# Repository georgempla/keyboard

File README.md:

# George’s Keyboard

After many hours of work, I designed a custom mechanical keyboard featuring RGB LEDs, OLED displays, and rotary encoders. This project focuses on PCB planning, firmware research, CAD design, and represents my second hardware project ever.

---

## What This Project Is

This Project is a custom mechanical keyboard powered by a Raspberry Pi Pico. It has:
- Sections of addressable RGB LEDs
- Two rotary encoders with switches
- An OLED 0.91Inch display
- A custom PCB designed in KiCad
- A 3D-printed case that showcases the PCB

The goal of this project was to recreate my own keyboard layout while adding extra functionality and learning more about PCB design and KMK firmware.

---

## Inspiration

This was only my second project ever. While looking for ideas I realized that the inspiration was right in front of me: my own keyboard. After taking measurements and studying how keyboards in general are designed, I decided to recreate it while adding my own twist on the concept with LEDs, an OLED display, and rotary encoders.

---

## Challenges / What I Learned

This was the second PCB I havee ever designed, and the first one I designed completely on my own. Through this process, I learned:
- How to organize a KiCad project properly
- Better routing techniques
- How to recover from mistakes and reroute a board cleanly

Even though I had to redo parts of the design, the second iteration was much cleaner.

---

## Design Files

This project includes:
- A full keyboard schematic
- A routed PCB layout
- A 3D printable case design

Schematic | PCB Layout | Case
:--:|:--:|:--:
 |  |  

---

## Firmware (Planned)

The firmware is currently written but *untested*, as the keyboard has not yet been assembled. Once the hardware is built I plan to:
- Flash the firmware to the Raspberry Pi Pico
- Test all keys, LEDs, encoders, and the OLED display
- Fix bugs and upload a finalized version

After testing this section will be updated with corrected code and flashing instructions.

---

## Bill of Materials (BOM)

### Electronics
- 1× Raspberry Pi Pico
- 1× OLED module (0.91", 128×32)
- 2× Rotary encoders (12 mm, 24 P/R, with switch)
- 10× SK6812 RGB LEDs
- 2× 74HCT595D shift registers
- 1× 74AHCT125
- 110× 1N4148 diodes
- 1× 1000 µF capacitor
- 2× 100 nF ceramic capacitors

### Mechanical
- Keychron K Pro switches (110 pieces)
- Glorious Stabilizers V2
- Mountain Dolomite A Backlit Keycap Set
- 3D printed case (`case.stl`)

---

## Next Steps

- Wait for approval
- Order the PCB
- Print the case
- Assemble and solder all components
- Test and debug firmware
- Update this README with build instructions

---

## Reflection

This project helped me evolve a lot as a designer. Compared to my first PCB, this one is cleaner, more complex, and better planned. Even though it isn't built yet, I learned a huge amount about schematics, routing, and hardware design through the process.

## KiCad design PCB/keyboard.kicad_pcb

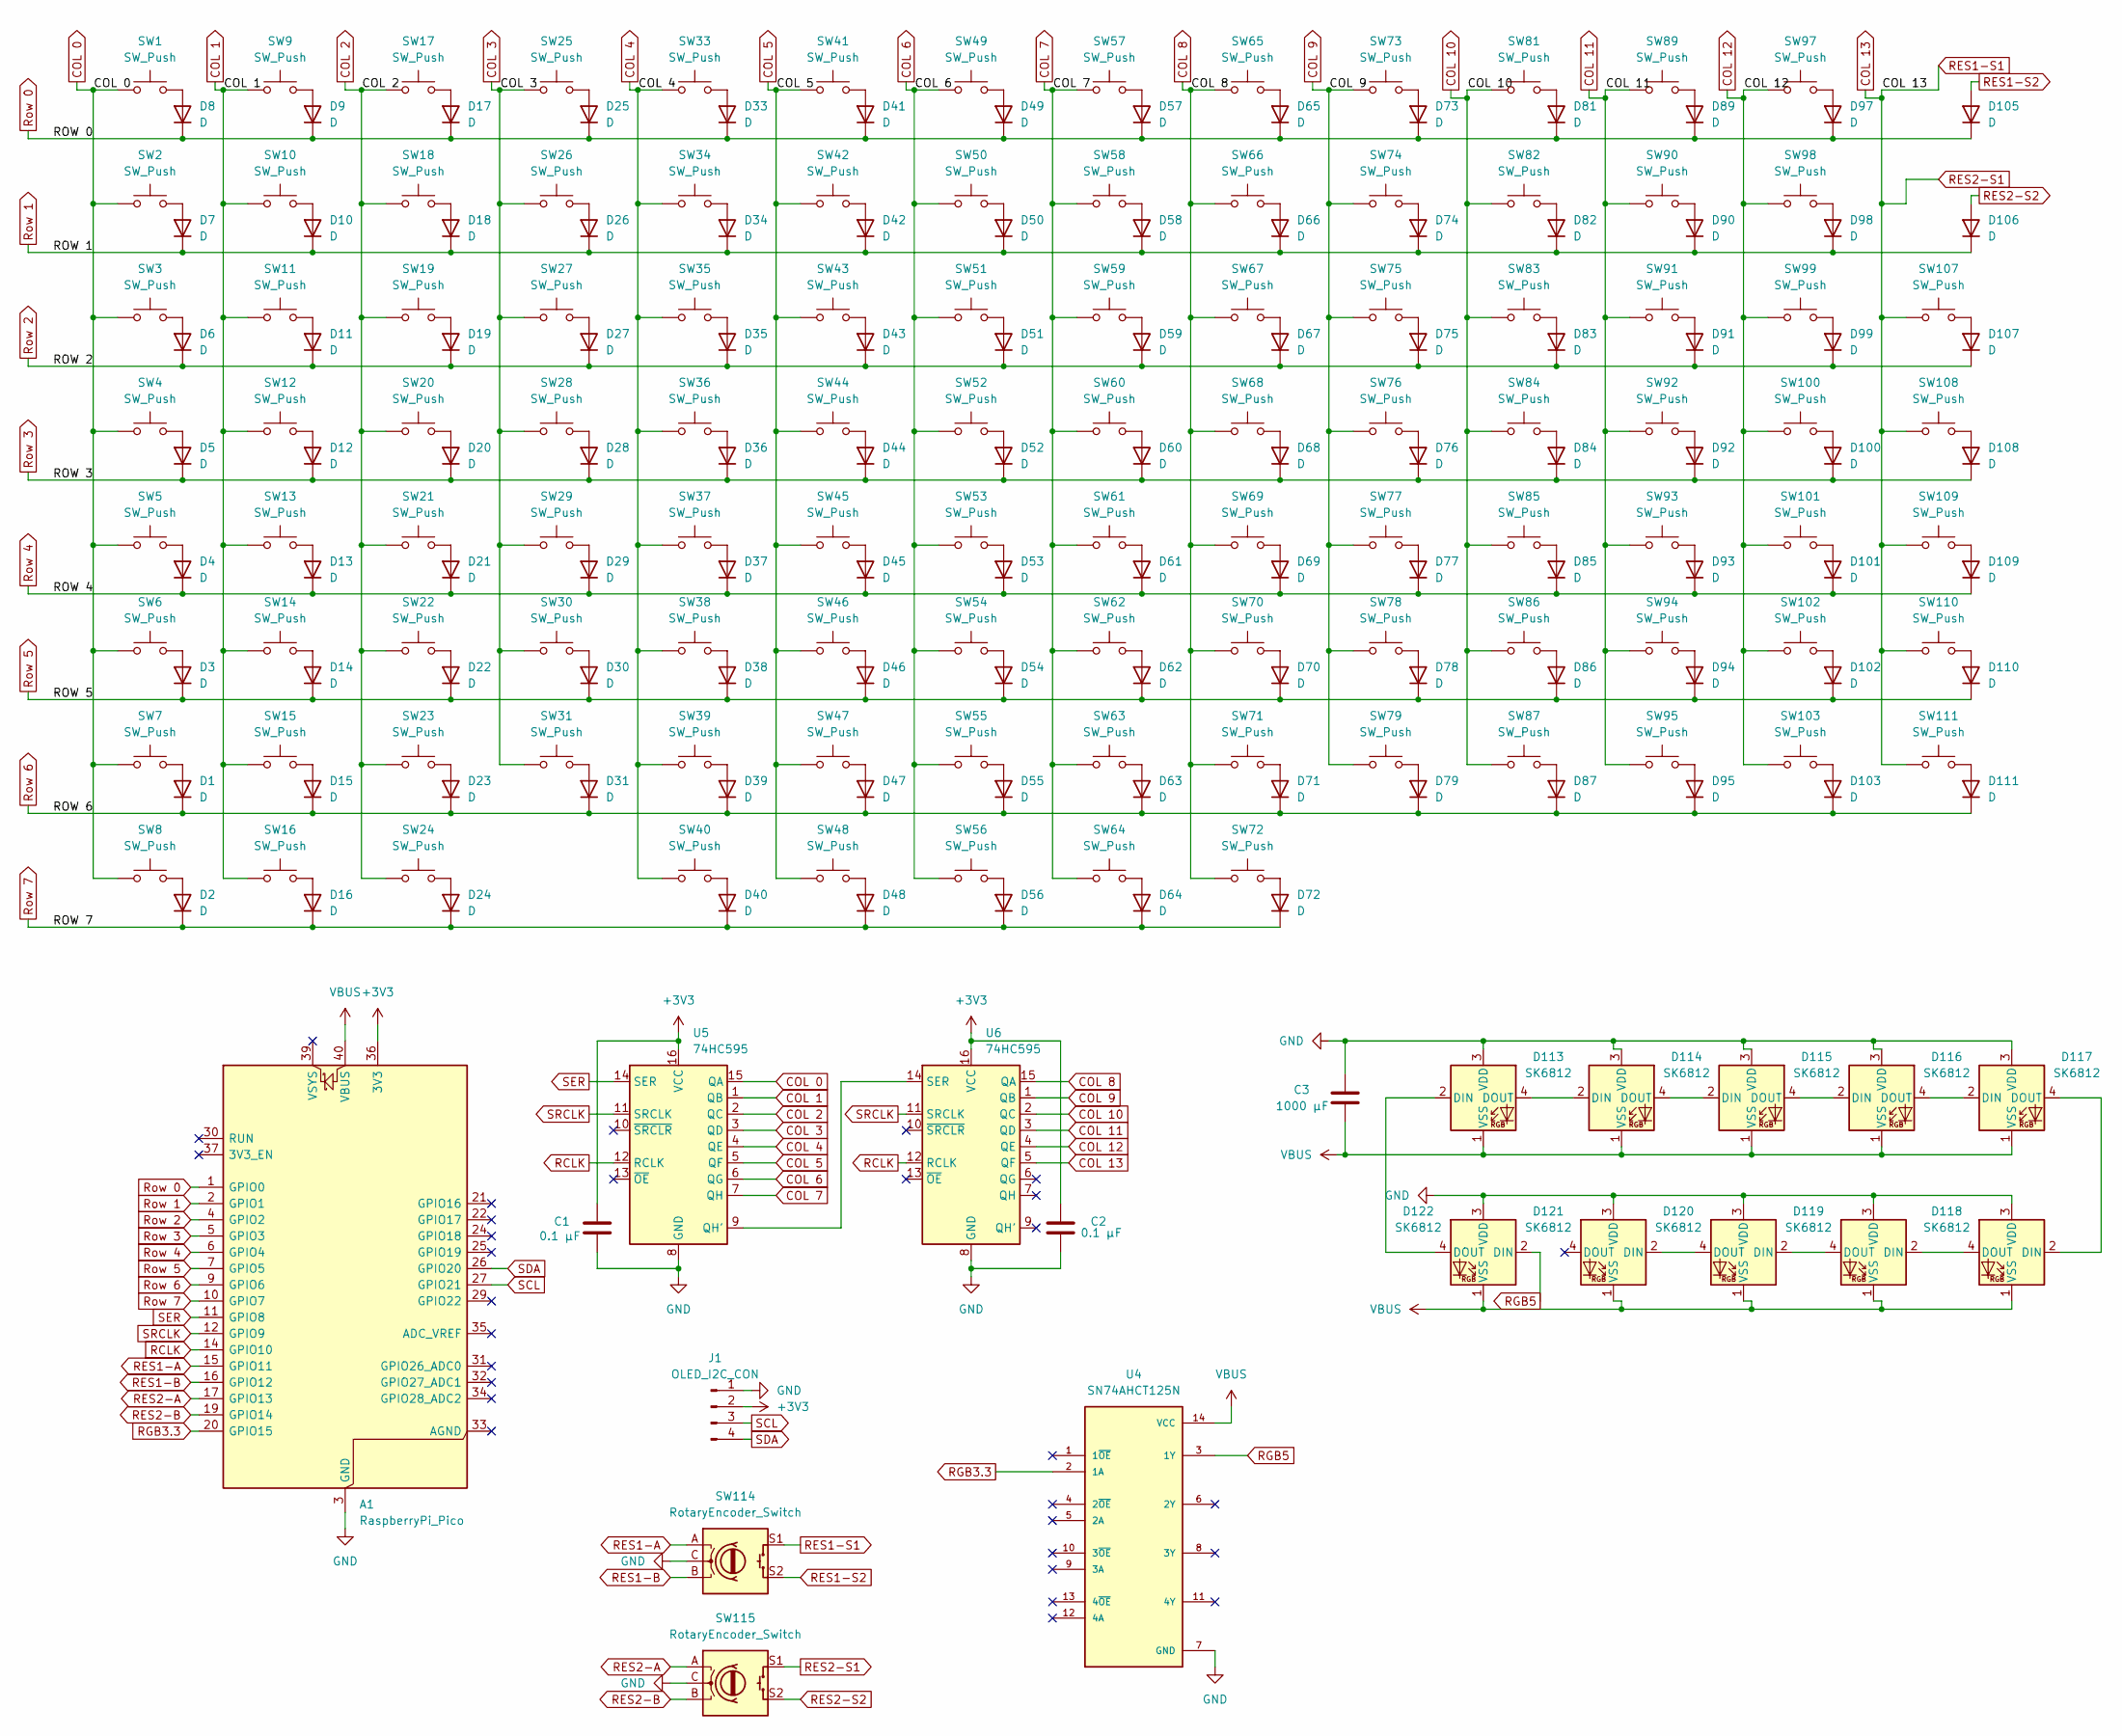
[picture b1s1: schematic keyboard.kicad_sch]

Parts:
A1: RaspberryPi_Pico; RaspberryPi_Pico_Common_Unspecified
C1, C2: 0.1 µF; C_Disc_D5.0mm_W2.5mm_P5.00mm
C3: 1000 µF; CP_Radial_D8.0mm_P3.50mm
D1, D2, D3, D4, D5, D6, D7, D8, D9, D10, D11, D12, D13, D14, D15, D16, D17, D18, D19, D20, D21, D22, D23, D24, D25, D26, D27, D28, D29, D30, D31, D33, D34, D35, D36, D37, D38, D39, D40, D41, D42, D43, D44, D45, D46, D47, D48, D49, D50, D51, D52, D53, D54, D55, D56, D57, D58, D59, D60, D61, D62, D63, D64, D65, D66, D67, D68, D69, D70, D71, D72, D73, D74, D75, D76, D77, D78, D79, D81, D82, D83, D84, D85, D86, D87, D89, D90, D91, D92, D93, D94, D95, D97, D98, D99, D100, D101, D102, D103, D105, D106, D107, D108, D109, D110, D111: D; D_DO-35_SOD27_P7.62mm_Horizontal
D113, D114, D115, D116, D117, D118, D119, D120, D121, D122: SK6812; LED_SK6812_PLCC4_5.0x5.0mm_P3.2mm
J1: OLED_I2C_CON; 0.91 OLED 128x32
SW1, SW2, SW3, SW4, SW5, SW6, SW7, SW8, SW9, SW10, SW11, SW12, SW13, SW14, SW15, SW16, SW17, SW18, SW19, SW20, SW21, SW22, SW23, SW24, SW25, SW26, SW27, SW28, SW29, SW30, SW31, SW33, SW34, SW35, SW36, SW37, SW38, SW39, SW40, SW41, SW42, SW43, SW44, SW45, SW46, SW47, SW48, SW49, SW50, SW51, SW52, SW53, SW54, SW55, SW56, SW57, SW58, SW59, SW60, SW61, SW62, SW63, SW64, SW65, SW66, SW67, SW68, SW69, SW70, SW71, SW72, SW73, SW74, SW75, SW76, SW77, SW78, SW79, SW81, SW82, SW83, SW84, SW85, SW86, SW87, SW89, SW90, SW91, SW92, SW93, SW94, SW95, SW97, SW98, SW99, SW100, SW101, SW102, SW103, SW107, SW108, SW109, SW110, SW111: SW_Push; SW_Cherry_MX_1.00u_PCB
SW114, SW115: RotaryEncoder_Switch; RotaryEncoder_Alps_EC12E-Switch_Vertical_H20mm
U4: SN74AHCT125N; DIP794W45P254L1930H508Q14; PARTREV Q
U5, U6: 74HC595; SOIC127P600X175-16N

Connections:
+3V3: A1.36 (3V3), C1.1, C2.1, J1.2, U5.16 (VCC), U6.16 (VCC)
COL 0: SW1.1, SW2.1, SW3.1, SW4.1, SW5.1, SW6.1, SW7.1, SW8.1, U5.15 (QA)
COL 1: SW9.1, SW10.1, SW11.1, SW12.1, SW13.1, SW14.1, SW15.1, SW16.1, U5.1 (QB)
COL 2: SW17.1, SW18.1, SW19.1, SW20.1, SW21.1, SW22.1, SW23.1, SW24.1, U5.2 (QC)
COL 3: SW25.1, SW26.1, SW27.1, SW28.1, SW29.1, SW30.1, SW31.1, U5.3 (QD)
COL 4: SW33.1, SW34.1, SW35.1, SW36.1, SW37.1, SW38.1, SW39.1, SW40.1, U5.4 (QE)
COL 5: SW41.1, SW42.1, SW43.1, SW44.1, SW45.1, SW46.1, SW47.1, SW48.1, U5.5 (QF)
COL 6: SW49.1, SW50.1, SW51.1, SW52.1, SW53.1, SW54.1, SW55.1, SW56.1, U5.6 (QG)
COL 7: SW57.1, SW58.1, SW59.1, SW60.1, SW61.1, SW62.1, SW63.1, SW64.1, U5.7 (QH)
COL 8: SW65.1, SW66.1, SW67.1, SW68.1, SW69.1, SW70.1, SW71.1, SW72.1, U6.15 (QA)
COL 9: SW73.1, SW74.1, SW75.1, SW76.1, SW77.1, SW78.1, SW79.1, U6.1 (QB)
COL 10: SW81.1, SW82.1, SW83.1, SW84.1, SW85.1, SW86.1, SW87.1, U6.2 (QC)
COL 11: SW89.1, SW90.1, SW91.1, SW92.1, SW93.1, SW94.1, SW95.1, U6.3 (QD)
COL 12: SW97.1, SW98.1, SW99.1, SW100.1, SW101.1, SW102.1, SW103.1, U6.4 (QE)
COL 13: SW107.1, SW108.1, SW109.1, SW110.1, SW111.1, SW114.S1, SW115.S1, U6.5 (QF)
GND: A1.3 (GND), A1.8 (GND), A1.13 (GND), A1.18 (GND), A1.23 (GND), A1.28 (GND), A1.38 (GND), C1.2, C2.2, C3.1, D113.3 (VDD), D114.3 (VDD), D115.3 (VDD), D116.3 (VDD), D117.3 (VDD), D118.3 (VDD), D119.3 (VDD), D120.3 (VDD), D121.3 (VDD), D122.3 (VDD), J1.1, SW114.C, SW115.C, U4.7 (GND), U5.8 (GND), U6.8 (GND)
unnamed: D1.2 (A), SW7.2
unnamed: D2.2 (A), SW8.2
unnamed: D3.2 (A), SW6.2
unnamed: D4.2 (A), SW5.2
unnamed: D5.2 (A), SW4.2
unnamed: D6.2 (A), SW3.2
unnamed: D7.2 (A), SW2.2
unnamed: D8.2 (A), SW1.2
unnamed: D9.2 (A), SW9.2
unnamed: D10.2 (A), SW10.2
unnamed: D11.2 (A), SW11.2
unnamed: D12.2 (A), SW12.2
unnamed: D13.2 (A), SW13.2
unnamed: D14.2 (A), SW14.2
unnamed: D15.2 (A), SW15.2
unnamed: D16.2 (A), SW16.2
unnamed: D17.2 (A), SW17.2
unnamed: D18.2 (A), SW18.2
unnamed: D19.2 (A), SW19.2
unnamed: D20.2 (A), SW20.2
unnamed: D21.2 (A), SW21.2
unnamed: D22.2 (A), SW22.2
unnamed: D23.2 (A), SW23.2
unnamed: D24.2 (A), SW24.2
unnamed: D25.2 (A), SW25.2
unnamed: D26.2 (A), SW26.2
unnamed: D27.2 (A), SW27.2
unnamed: D28.2 (A), SW28.2
unnamed: D29.2 (A), SW29.2
unnamed: D30.2 (A), SW30.2
unnamed: D31.2 (A), SW31.2
unnamed: D33.2 (A), SW33.2
unnamed: D34.2 (A), SW34.2
unnamed: D35.2 (A), SW35.2
unnamed: D36.2 (A), SW36.2
unnamed: D37.2 (A), SW37.2
unnamed: D38.2 (A), SW38.2
unnamed: D39.2 (A), SW39.2
unnamed: D40.2 (A), SW40.2
unnamed: D41.2 (A), SW41.2
unnamed: D42.2 (A), SW42.2
unnamed: D43.2 (A), SW43.2
unnamed: D44.2 (A), SW44.2
unnamed: D45.2 (A), SW45.2
unnamed: D46.2 (A), SW46.2
unnamed: D47.2 (A), SW47.2
unnamed: D48.2 (A), SW48.2
unnamed: D49.2 (A), SW49.2
unnamed: D50.2 (A), SW50.2
unnamed: D51.2 (A), SW51.2
unnamed: D52.2 (A), SW52.2
unnamed: D53.2 (A), SW53.2
unnamed: D54.2 (A), SW54.2
unnamed: D55.2 (A), SW55.2
unnamed: D56.2 (A), SW56.2
unnamed: D57.2 (A), SW57.2
unnamed: D58.2 (A), SW58.2
unnamed: D59.2 (A), SW59.2
unnamed: D60.2 (A), SW60.2
unnamed: D61.2 (A), SW61.2
unnamed: D62.2 (A), SW62.2
unnamed: D63.2 (A), SW63.2
unnamed: D64.2 (A), SW64.2
unnamed: D65.2 (A), SW65.2
unnamed: D66.2 (A), SW66.2
unnamed: D67.2 (A), SW67.2
unnamed: D68.2 (A), SW68.2
unnamed: D69.2 (A), SW69.2
unnamed: D70.2 (A), SW70.2
unnamed: D71.2 (A), SW71.2
unnamed: D72.2 (A), SW72.2
unnamed: D73.2 (A), SW73.2
unnamed: D74.2 (A), SW74.2
unnamed: D75.2 (A), SW75.2
unnamed: D76.2 (A), SW76.2
unnamed: D77.2 (A), SW77.2
unnamed: D78.2 (A), SW78.2
unnamed: D79.2 (A), SW79.2
unnamed: D81.2 (A), SW81.2
unnamed: D82.2 (A), SW82.2
unnamed: D83.2 (A), SW83.2
unnamed: D84.2 (A), SW84.2
unnamed: D85.2 (A), SW85.2
unnamed: D86.2 (A), SW86.2
unnamed: D87.2 (A), SW87.2
unnamed: D89.2 (A), SW89.2
unnamed: D90.2 (A), SW90.2
unnamed: D91.2 (A), SW91.2
unnamed: D92.2 (A), SW92.2
unnamed: D93.2 (A), SW93.2
unnamed: D94.2 (A), SW94.2
unnamed: D95.2 (A), SW95.2
unnamed: D97.2 (A), SW97.2
unnamed: D98.2 (A), SW98.2
unnamed: D99.2 (A), SW99.2
unnamed: D100.2 (A), SW100.2
unnamed: D101.2 (A), SW101.2
unnamed: D102.2 (A), SW102.2
unnamed: D103.2 (A), SW103.2
unnamed: D107.2 (A), SW107.2
unnamed: D108.2 (A), SW108.2
unnamed: D109.2 (A), SW109.2
unnamed: D110.2 (A), SW110.2
unnamed: D111.2 (A), SW111.2
unnamed: D113.2 (DIN), D122.4 (DOUT)
unnamed: D113.4 (DOUT), D114.2 (DIN)
unnamed: D114.4 (DOUT), D115.2 (DIN)
unnamed: D115.4 (DOUT), D116.2 (DIN)
unnamed: D116.4 (DOUT), D117.2 (DIN)
unnamed: D117.4 (DOUT), D118.2 (DIN)
unnamed: D118.4 (DOUT), D119.2 (DIN)
unnamed: D119.4 (DOUT), D120.2 (DIN)
unnamed: D120.4 (DOUT), D121.2 (DIN)
unnamed: U5.9 (QH'), U6.14 (SER)
RCLK: A1.14 (GPIO10), U5.12 (RCLK), U6.12 (RCLK)
RES1-A: A1.15 (GPIO11), SW114.A
RES1-B: A1.16 (GPIO12), SW114.B
RES1-S2: D105.2 (A), SW114.S2
RES2-A: A1.17 (GPIO13), SW115.A
RES2-B: A1.19 (GPIO14), SW115.B
RES2-S2: D106.2 (A), SW115.S2
RGB3.3: A1.20 (GPIO15), U4.2 (1A)
RGB5: D122.2 (DIN), U4.3 (1Y)
Row 0: A1.1 (GPIO0), D8.1 (K), D9.1 (K), D17.1 (K), D25.1 (K), D33.1 (K), D41.1 (K), D49.1 (K), D57.1 (K), D65.1 (K), D73.1 (K), D81.1 (K), D89.1 (K), D97.1 (K), D105.1 (K)
Row 1: A1.2 (GPIO1), D7.1 (K), D10.1 (K), D18.1 (K), D26.1 (K), D34.1 (K), D42.1 (K), D50.1 (K), D58.1 (K), D66.1 (K), D74.1 (K), D82.1 (K), D90.1 (K), D98.1 (K), D106.1 (K)
Row 2: A1.4 (GPIO2), D6.1 (K), D11.1 (K), D19.1 (K), D27.1 (K), D35.1 (K), D43.1 (K), D51.1 (K), D59.1 (K), D67.1 (K), D75.1 (K), D83.1 (K), D91.1 (K), D99.1 (K), D107.1 (K)
Row 3: A1.5 (GPIO3), D5.1 (K), D12.1 (K), D20.1 (K), D28.1 (K), D36.1 (K), D44.1 (K), D52.1 (K), D60.1 (K), D68.1 (K), D76.1 (K), D84.1 (K), D92.1 (K), D100.1 (K), D108.1 (K)
Row 4: A1.6 (GPIO4), D4.1 (K), D13.1 (K), D21.1 (K), D29.1 (K), D37.1 (K), D45.1 (K), D53.1 (K), D61.1 (K), D69.1 (K), D77.1 (K), D85.1 (K), D93.1 (K), D101.1 (K), D109.1 (K)
Row 5: A1.7 (GPIO5), D3.1 (K), D14.1 (K), D22.1 (K), D30.1 (K), D38.1 (K), D46.1 (K), D54.1 (K), D62.1 (K), D70.1 (K), D78.1 (K), D86.1 (K), D94.1 (K), D102.1 (K), D110.1 (K)
Row 6: A1.9 (GPIO6), D1.1 (K), D15.1 (K), D23.1 (K), D31.1 (K), D39.1 (K), D47.1 (K), D55.1 (K), D63.1 (K), D71.1 (K), D79.1 (K), D87.1 (K), D95.1 (K), D103.1 (K), D111.1 (K)
Row 7: A1.10 (GPIO7), D2.1 (K), D16.1 (K), D24.1 (K), D40.1 (K), D48.1 (K), D56.1 (K), D64.1 (K), D72.1 (K)
SCL: A1.27 (GPIO21), J1.3
SDA: A1.26 (GPIO20), J1.4
SER: A1.11 (GPIO8), U5.14 (SER)
SRCLK: A1.12 (GPIO9), U5.11 (SRCLK), U6.11 (SRCLK)
VBUS: A1.40 (VBUS), C3.2, D113.1 (VSS), D114.1 (VSS), D115.1 (VSS), D116.1 (VSS), D117.1 (VSS), D118.1 (VSS), D119.1 (VSS), D120.1 (VSS), D121.1 (VSS), D122.1 (VSS), U4.14 (VCC)

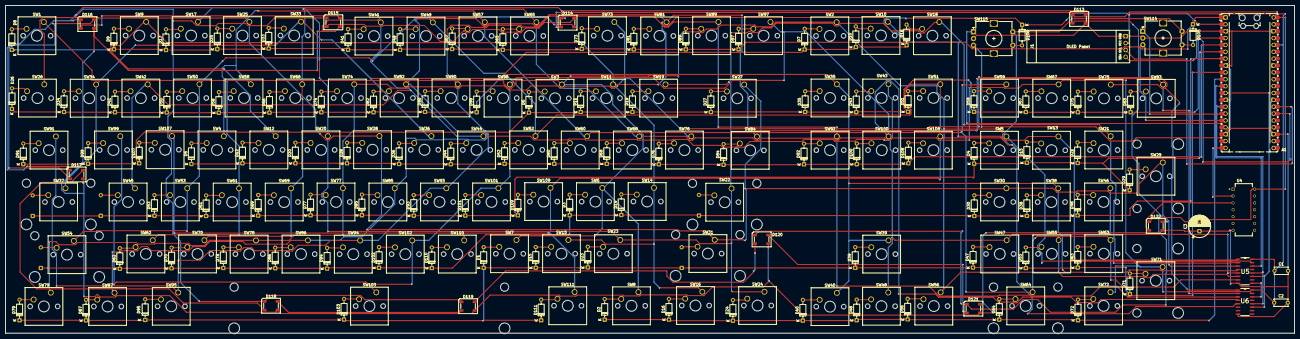
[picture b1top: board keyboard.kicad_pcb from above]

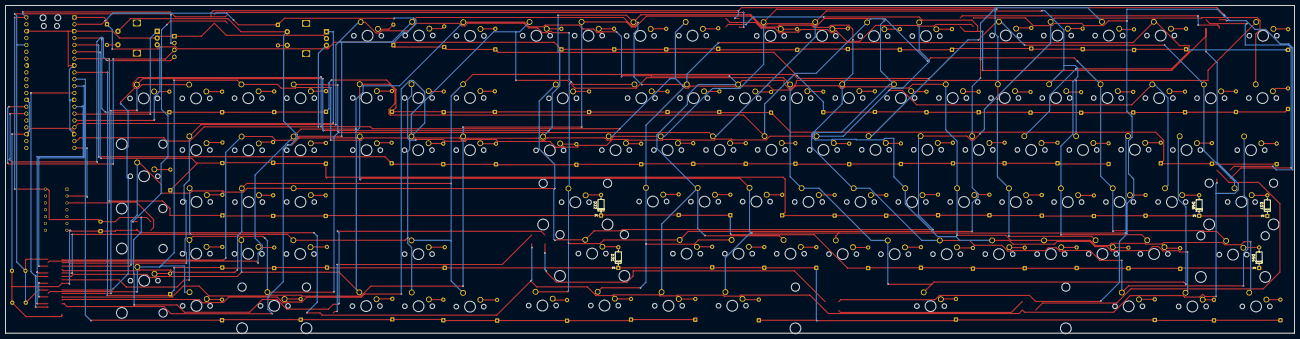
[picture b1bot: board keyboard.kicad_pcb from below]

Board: 2 copper layers, 476.7 x 121.2 mm, 230 parts (5 on the bottom side), 152 nets.

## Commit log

2026-01-07 initial schematic upload
2026-01-14 First iteration
2026-01-15 added bom .csv
2026-01-16 Updated BOM to include product links
